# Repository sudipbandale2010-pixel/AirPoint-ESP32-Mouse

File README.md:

# AirPoint-ESP32-Mouse
This is an easy ESP32 Air mouse project which uses BLE (Bluetooth Low Energy) for connecting to any other devices like Laptop, PC, Smart TVs, Projectors, and even mobiles and tablets. So we can say that its universal Air mouse.

<details>
<summary>Bill of Materials (BOM)</summary>

| Item | Purpose | Source | Cost |
|------|---------|---------|------|
| ESP32 Dev Module | Main microcontroller | Amazon | $5.70 |
| 12x12mm Tactile Push Buttons (x4) | Left click, right click, scroll up, scroll down | Amazon | $0.87 |
| TP4056 Charging Module | Battery charging | Amazon | $1.32 |
| 3.7V Li-ion Battery (18650) | Power source | Amazon | $4.14 |
| MPU6050 Accelerometer/Gyroscope | Motion detection | Amazon | $3.00 |
| PLA Filament | 3D printed enclosure | Amazon | $7.25 |
| PCB | Custom circuit board | JLCPCB | $6.40 |
| **TOTAL COST** |  |  | **$25.39** |

</details>

Wiring diagram:-

Once completing the circuit diagram and coding, I was wondering if it works, so I made a prototype version of AirPoint with breadboard.

Now the thing was, It worked perfectly but I had powered it with USB Cable and I wanted such battery which would give more power and for long time, so I started working on it.

And now, I was going to use the 18650 li-ion battery 3.7v with 3000mAh and Tp4056 charging module for charging which perfectly worked fine. 

Now the time was to make my own custom case for it, So I started designing one and it looked like this...

If you want, you can even change the colours of the case accordingly, as I have provided the file of CAD, you can now print the case with ease.

Now the thing is, I am using breadboard for the final project and you can too but if you are feeling lazy then you can use PCB too, so I have provided the PCB gerber files and it may cost around 6-7$ (Depends from where you are buying it,I used JLC PCB), This is how the PCB will look like...

(NOTE :- If you are really using PCB for project then do remember to attach wires from switch to the PCB as the PCB will be at the bottom of the case and Switch may not reach the sufficient height.)

That's it!!, You just created your own ESP32 based Air Mouse and now you are ready to use it. 

How to use it? 
Turn on the bluetooth of device(ex- phone or smart TV), and connect the device with AirPoint, You will see that the cursor is moving by the AirPoint, the upper two buttons are RMB and LMB, and the bottom and verticle buttons are for scrolling.

Why I built this:
For how long are we using the mouse which just rubs against the surface, to be futurastic, I made my own custom air mouse, AirPoint.

Here's the zine page of my Project....

see ya!!!! :)

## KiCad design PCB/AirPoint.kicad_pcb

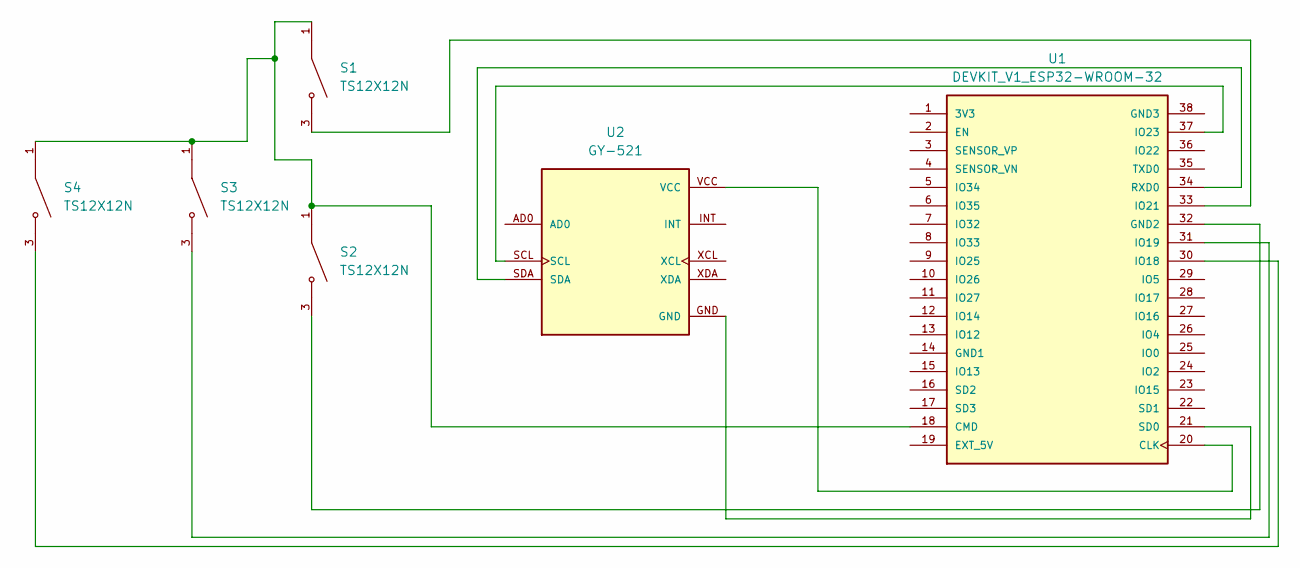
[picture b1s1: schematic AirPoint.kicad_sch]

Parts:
S1, S2, S3, S4: TS12X12N; SW_TS12X12N; PARTREV June 9, 2021
U1: DEVKIT_V1_ESP32-WROOM-32; MODULE_DEVKIT_V1_ESP32-WROOM-32; PARTREV N/A
U2: GY-521; MODULE_GY-521; PARTREV NA

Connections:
unnamed: U1.20 (CLK), U2.VCC
unnamed: S1.1, S1.2, S2.1, S2.2, S3.1, S3.2, S4.1, S4.2, U1.18 (CMD)
unnamed: S2.3, S2.4, U1.32 (GND2)
unnamed: S4.3, S4.4, U1.30 (IO18)
unnamed: S3.3, S3.4, U1.31 (IO19)
unnamed: S1.3, S1.4, U1.33 (IO21)
unnamed: U1.37 (IO23), U2.SCL
unnamed: U1.34 (RXD0), U2.SDA
unnamed: U1.21 (SD0), U2.GND

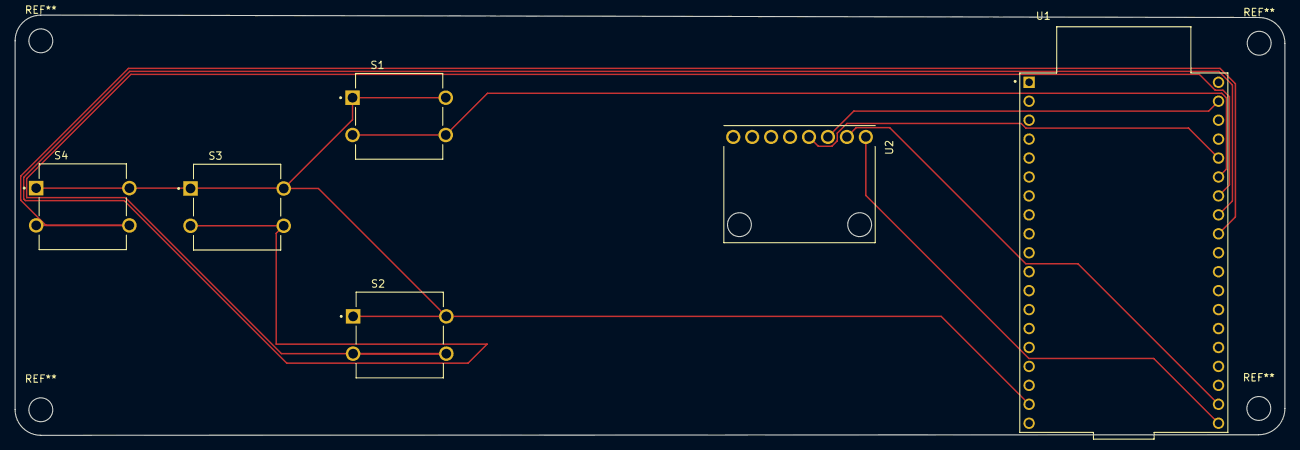
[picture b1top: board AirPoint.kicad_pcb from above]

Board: 2 copper layers, 170.3 x 56.4 mm, 6 parts (0 on the bottom side), 9 nets.

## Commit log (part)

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2026-06-06 Create Firmware
